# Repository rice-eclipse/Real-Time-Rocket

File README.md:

# Neutro Board
Repository stored on the raspberry pi used for Spaceport America Cup 2023 and launch test in Spring 2023. The scripts activates the sensors on Neutro, collects data, and transmit to the ground station NARWAL.

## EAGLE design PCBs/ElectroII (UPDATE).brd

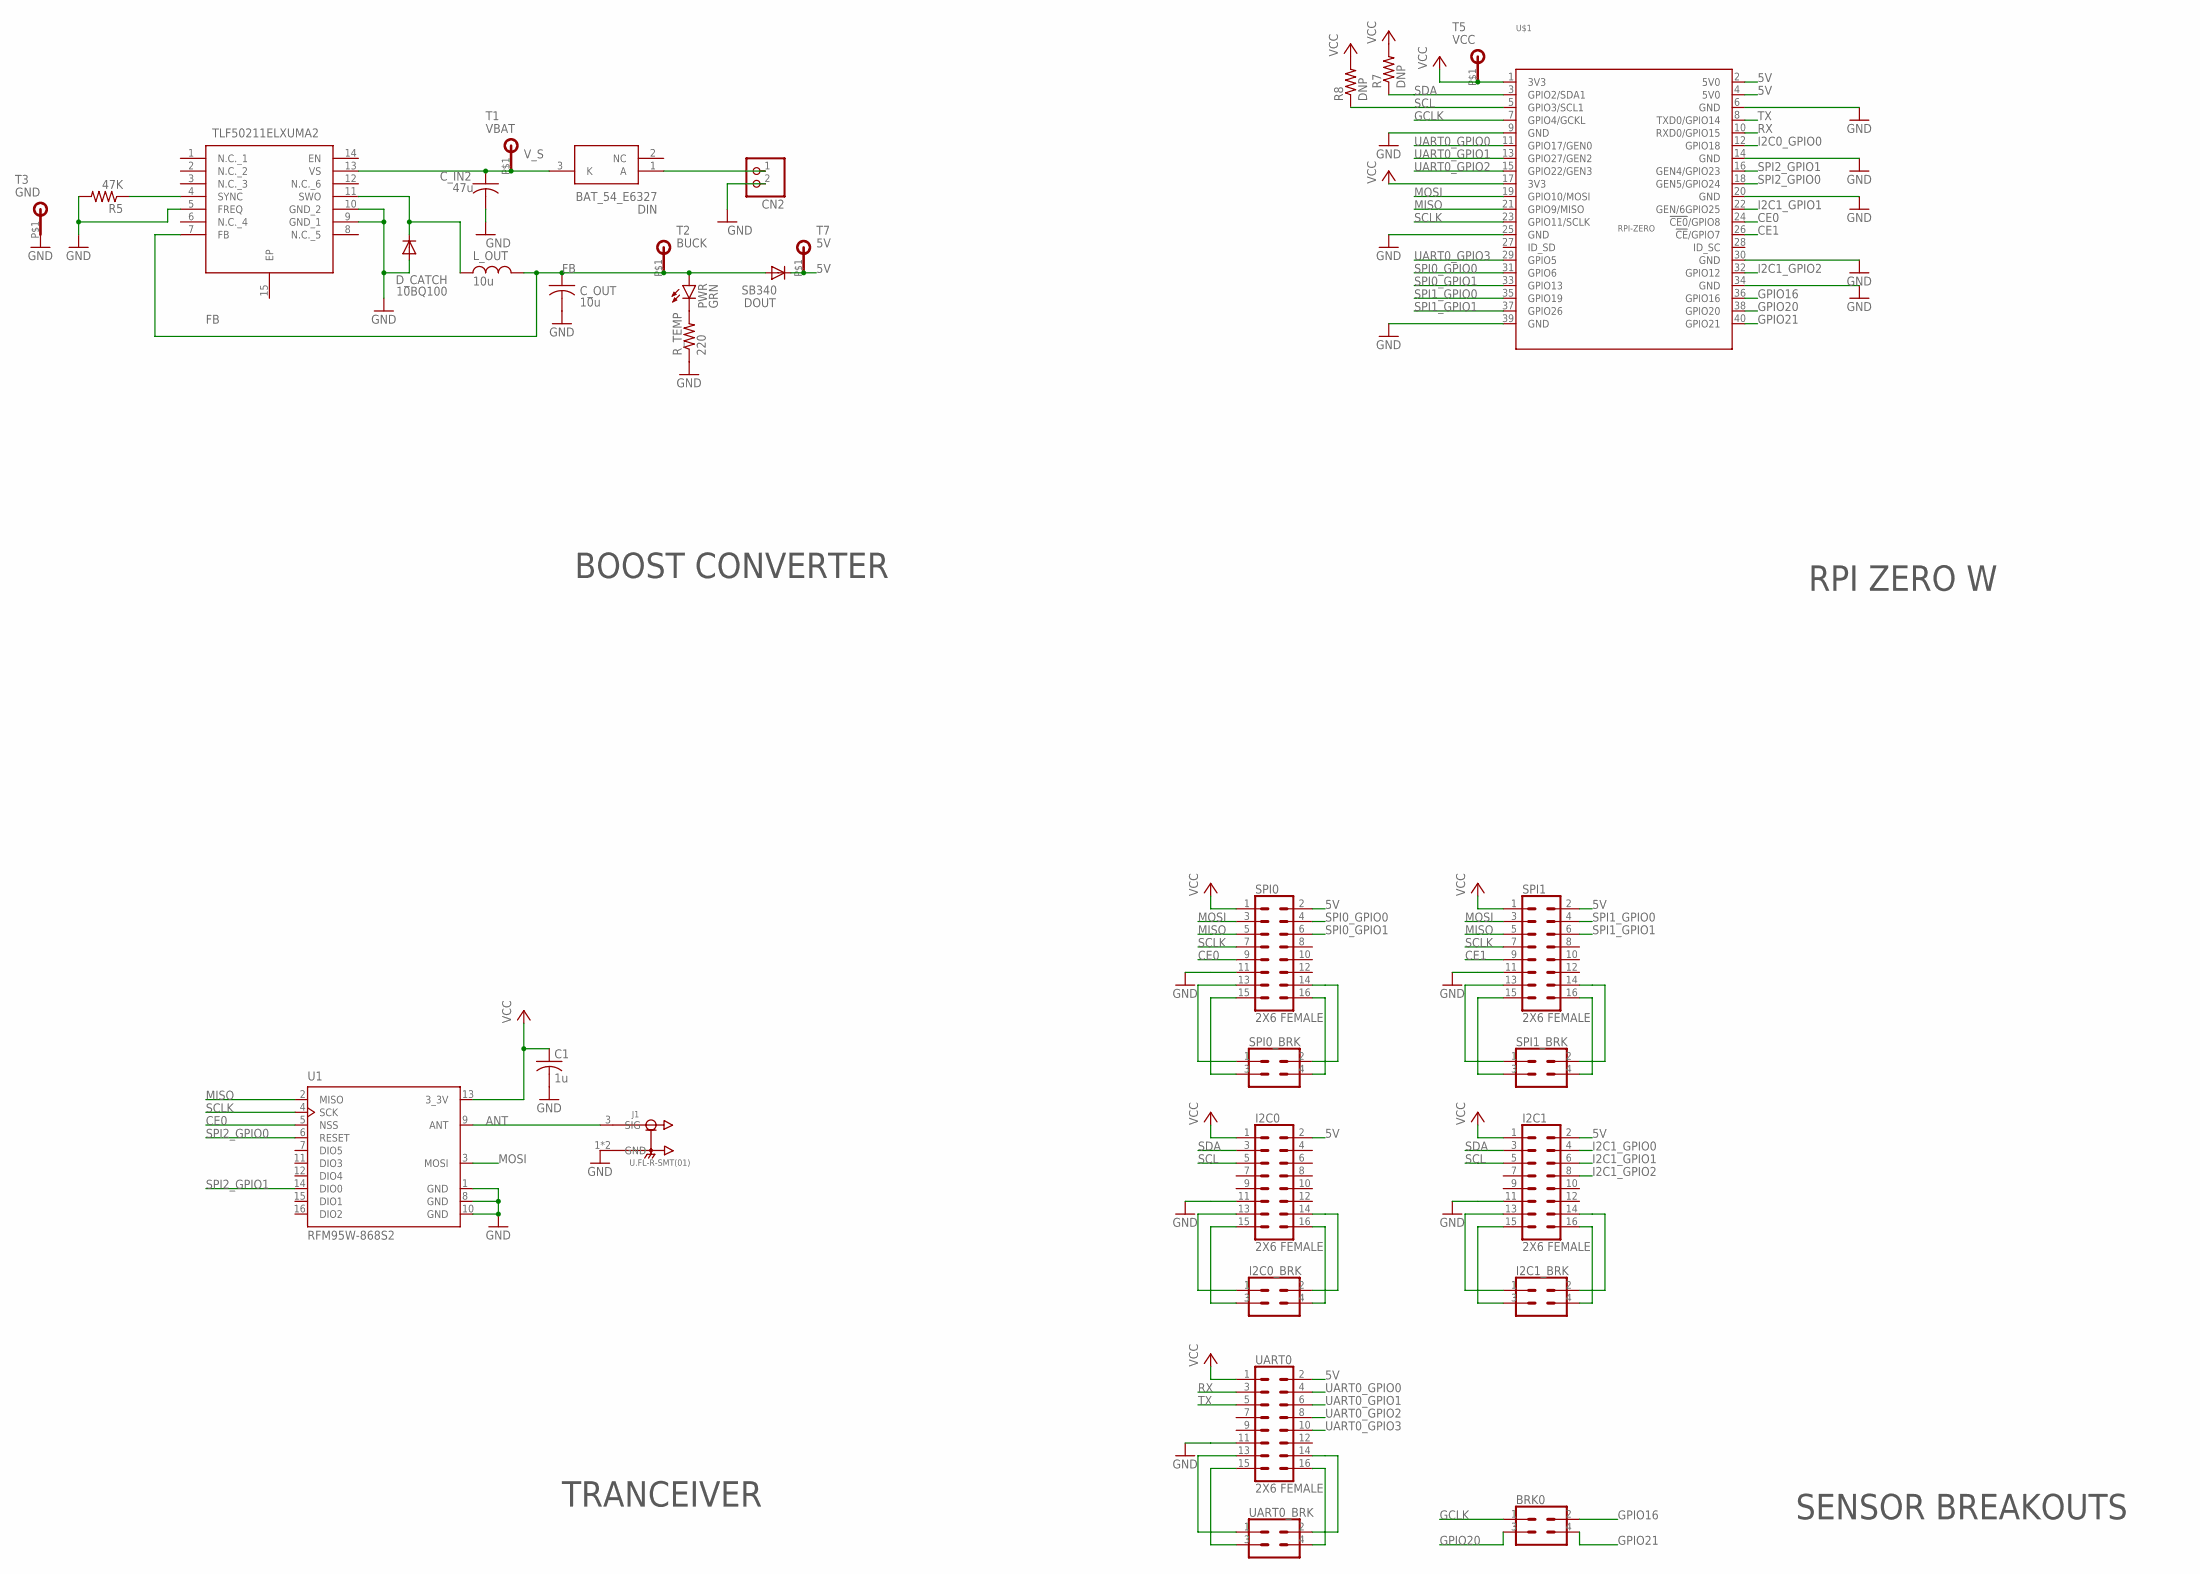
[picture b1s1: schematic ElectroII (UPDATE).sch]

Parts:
BRK0: SENSOR_PIN_BREAKOUT; 2X2
C1: 1u; C1206
CN2: JST_2PIN-SMT-RA; JST-PH-2-SMT-RA
C_IN2: 47u; C1206
C_OUT: 10u; C1206
DIN: BAT_54_E6327; SOT95P240X110-3N
DOUT: SB340; DO41-10
D_CATCH: 10BQ100; DO41-10
I2C0, I2C1: 2X6 FEMALE; 2X7
I2C0_BRK, I2C1_BRK: SENSOR_PIN_BREAKOUT; 2X2
IC1: TLF50211ELXUMA2; SOP65P600X170-15N
J1: U.FL-R-SMT(01); HRS_U.FL-R-SMT(01)
L_OUT: 10u; L-DS75LC
PWR: GRN; LED5MM
R5: 47K; R1206
R7, R8: DNP; R1206
R_TEMP: 220; R1206
SPI0, SPI1: 2X6 FEMALE; 2X7
SPI0_BRK, SPI1_BRK: SENSOR_PIN_BREAKOUT; 2X2
T1: VBAT; TEST_PAD
T2: BUCK; TEST_PAD
T3: GND; TEST_PAD
T5: VCC; TEST_PAD
T7: 5V; TEST_PAD
U1: RFM95W-868S2; XCVR_RFM95W-868S2
U$1: RPI-ZERO; RASP_PI_ZERO_BOARD_FULL
UART0: 2X6 FEMALE; 2X7
UART0_BRK: SENSOR_PIN_BREAKOUT; 2X2

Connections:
5V: DOUT.C, I2C0.2, I2C1.2, SPI0.2, SPI1.2, T7.P$1, U$1.2 (5V0), U$1.4 (5V0), UART0.2
ANT: J1.3 (SIG), U1.9 (ANT)
CE0: SPI0.9, U1.5 (NSS), U$1.24 (!CE0!/GPIO8)
CE1: SPI1.9, U$1.26 (!CE!/GPIO7)
FB: C_OUT.1, DOUT.A, IC1.7 (FB), L_OUT.P$2 (2), PWR.A, T2.P$1
GCLK: BRK0.1, U$1.7 (GPIO4/GCKL)
GND: C1.2, CN2.2 (1), C_IN2.2, C_OUT.2, D_CATCH.A, I2C0.11, I2C1.11, IC1.5 (FREQ), IC1.9 (GND_1), IC1.10 (GND_2), J1.1 (GND), J1.2 (GND), R5.2, R_TEMP.1, SPI0.11, SPI1.11, T3.P$1, U1.1 (GND), U1.8 (GND), U1.10 (GND), U$1.6 (GND), U$1.9 (GND), U$1.14 (GND), U$1.20 (GND), U$1.25 (GND), U$1.30 (GND), U$1.34 (GND), U$1.39 (GND), UART0.11
GPIO16: BRK0.2, U$1.36 (GPIO16)
GPIO20: BRK0.3, U$1.38 (GPIO20)
GPIO21: BRK0.4, U$1.40 (GPIO21)
I2C0_GPIO0: U$1.12 (GPIO18)
I2C1_GPIO0: I2C1.4
I2C1_GPIO1: I2C1.6, U$1.22 (GEN/6GPIO25)
I2C1_GPIO2: I2C1.8, U$1.32 (GPIO12)
MISO: SPI0.5, SPI1.5, U1.2 (MISO), U$1.21 (GPIO9/MISO)
MOSI: SPI0.3, SPI1.3, U1.3 (MOSI), U$1.19 (GPIO10/MOSI)
unnamed: CN2.1 (2), DIN.1 (A)
unnamed: IC1.4 (SYNC), R5.1
unnamed: PWR.K (C), R_TEMP.2
unnamed: SPI0.15, SPI0_BRK.3
unnamed: D_CATCH.C, IC1.11 (SWO), L_OUT.P$1 (1)
unnamed: SPI0.16, SPI0_BRK.4
unnamed: SPI1.13, SPI1_BRK.1
unnamed: SPI0.13, SPI0_BRK.1
unnamed: SPI1.14, SPI1_BRK.2
unnamed: SPI0.14, SPI0_BRK.2
unnamed: SPI1.15, SPI1_BRK.3
unnamed: SPI1.16, SPI1_BRK.4
unnamed: I2C0.13, I2C0_BRK.1
unnamed: I2C0.14, I2C0_BRK.2
unnamed: I2C0.15, I2C0_BRK.3
unnamed: I2C0.16, I2C0_BRK.4
unnamed: I2C1.13, I2C1_BRK.1
unnamed: I2C1.14, I2C1_BRK.2
unnamed: I2C1.15, I2C1_BRK.3
unnamed: I2C1.16, I2C1_BRK.4
unnamed: UART0.13, UART0_BRK.1
unnamed: UART0.14, UART0_BRK.2
unnamed: UART0.15, UART0_BRK.3
unnamed: UART0.16, UART0_BRK.4
RX: U$1.10 (RXD0/GPIO15), UART0.3
SCL: I2C0.5, I2C1.5, R8.1, U$1.5 (GPIO3/SCL1)
SCLK: SPI0.7, SPI1.7, U1.4 (SCK), U$1.23 (GPIO11/SCLK)
SDA: I2C0.3, I2C1.3, R7.1, U$1.3 (GPIO2/SDA1)
SPI0_GPIO0: SPI0.4, U$1.31 (GPIO6)
SPI0_GPIO1: SPI0.6, U$1.33 (GPIO13)
SPI1_GPIO0: SPI1.4, U$1.35 (GPIO19)
SPI1_GPIO1: SPI1.6, U$1.37 (GPIO26)
SPI2_GPIO0: U1.6 (RESET), U$1.18 (GEN5/GPIO24)
SPI2_GPIO1: U1.14 (DIO0), U$1.16 (GEN4/GPIO23)
TX: U$1.8 (TXD0/GPIO14), UART0.5
UART0_GPIO0: U$1.11 (GPIO17/GEN0), UART0.4
UART0_GPIO1: U$1.13 (GPIO27/GEN2), UART0.6
UART0_GPIO2: U$1.15 (GPIO22/GEN3), UART0.8
UART0_GPIO3: U$1.29 (GPIO5), UART0.10
VCC: C1.1, I2C0.1, I2C1.1, R7.2, R8.2, SPI0.1, SPI1.1, T5.P$1, U1.13 (3_3V), U$1.1 (3V3), U$1.17 (3V3), UART0.1
V_S: C_IN2.1, DIN.3 (K), IC1.13 (VS), T1.P$1

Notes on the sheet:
SENSOR BREAKOUTS
RPI ZERO W
TRANCEIVER
BOOST CONVERTER

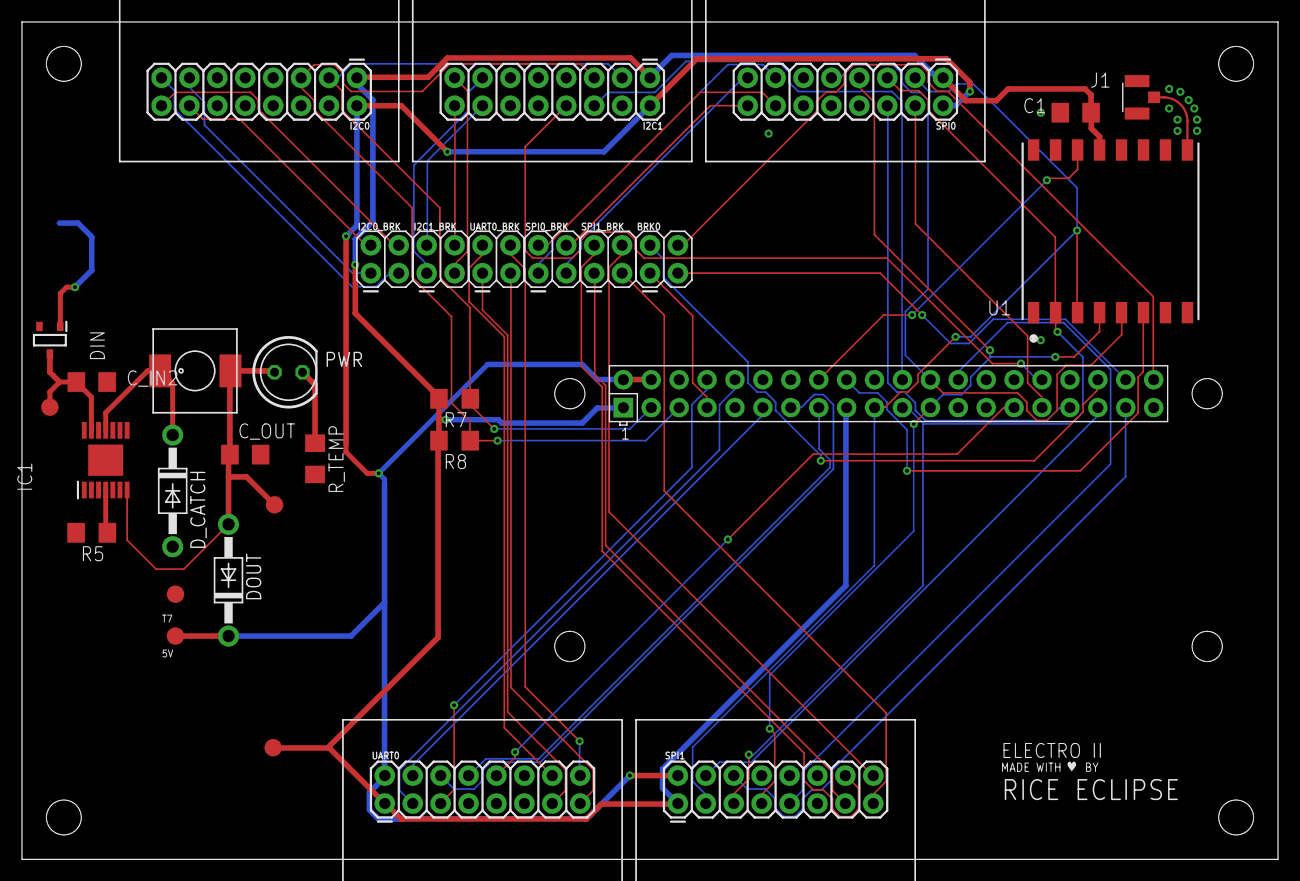
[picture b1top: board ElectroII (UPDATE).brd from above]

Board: 2 copper layers, 114.3 x 76.2 mm, 33 parts (1 on the bottom side), 55 nets.

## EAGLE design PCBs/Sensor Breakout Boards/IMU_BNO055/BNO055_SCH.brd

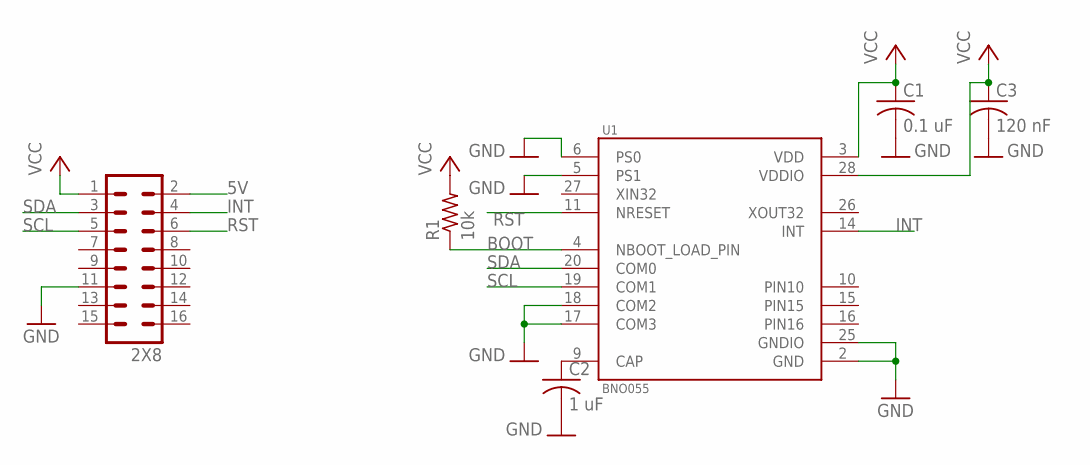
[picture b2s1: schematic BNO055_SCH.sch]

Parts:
2X8: MA08-2
C1: 0.1 uF; C1206
C2: 1 uF; C1206
C3: 120 nF; C1206
R1: 10k; R1206
U1: BNO055; LGA28R50P4X10_380X520X100

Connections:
5V: 2X8.2
BOOT: R1.1, U1.4 (NBOOT_LOAD_PIN)
GND: 2X8.11, C1.2, C2.2, C3.2, U1.2 (GND), U1.5 (PS1), U1.6 (PS0), U1.17 (COM3), U1.18 (COM2), U1.25 (GNDIO)
INT: 2X8.4, U1.14 (INT)
unnamed: C2.1, U1.9 (CAP)
PIN10: U1.10 (PIN10)
PIN15: U1.15 (PIN15)
PIN16: U1.16 (PIN16)
RST: 2X8.6, U1.11 (NRESET)
SCL: 2X8.5, U1.19 (COM1)
SDA: 2X8.3, U1.20 (COM0)
VCC: 2X8.1, C1.1, C3.1, R1.2, U1.3 (VDD), U1.28 (VDDIO)

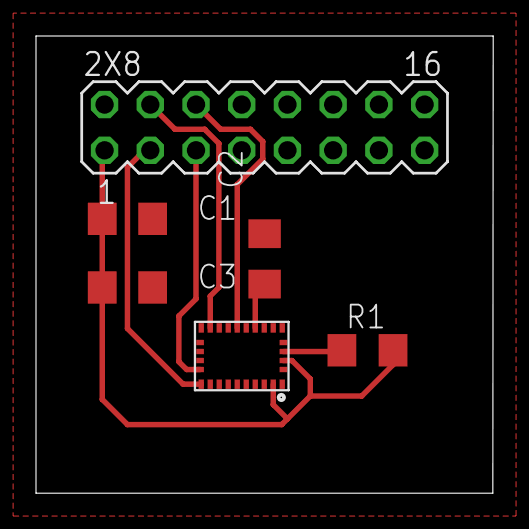
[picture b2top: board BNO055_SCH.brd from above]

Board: 2 copper layers, 25.4 x 25.4 mm, 6 parts (0 on the bottom side), 8 nets.

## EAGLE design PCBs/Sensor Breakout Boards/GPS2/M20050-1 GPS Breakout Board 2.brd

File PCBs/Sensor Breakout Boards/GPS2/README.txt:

Breakout Board for the Antenova GPS (M20050-1).
Plugged into the UART 1/2 Sensor Comm Port
Designed in EAGLE by Clayton Ramsey

Pin Description:
1. V (3v nominal)
2. Unused
3. Tx - output. Transmitter signal for UART.
4. HW_S. Used to enable standby mode.
5. Rx - input. Receiver signal for UART.
6. HW_R. System reset pin, active low
7. Unused
8. TM. Time markout, 1 P/s 
9. Unused
10. FIX - Indicates when a GPS fix is obtained
11. GND
12. Unused
13. Unused
14. Unused
15. Unused
16. Unused

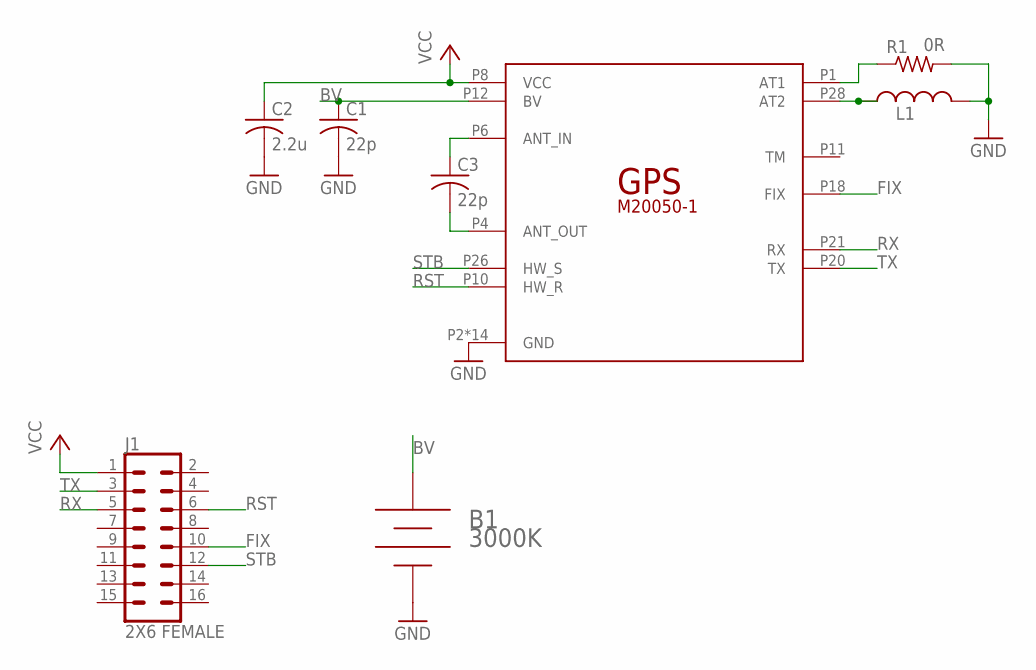
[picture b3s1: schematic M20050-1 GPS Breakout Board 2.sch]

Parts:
A1: GPS_M20050-1; M20050-1_GPS
B1: 3000K
C1, C3: 22p; C1206
C2: 2.2u; C1206
J1: 2X6 FEMALE; 2X7
L1: 1.8n; INDC2012X105N
R1: 0R; R1206

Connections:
BV: A1.P12 (BV), B1.+, C1.1
FIX: A1.P18 (FIX), J1.10
GND: A1.P2 (GND), A1.P3 (GND), A1.P5 (GND), A1.P7 (GND), A1.P9 (GND), A1.P15 (GND), A1.P16 (GND), A1.P17 (GND), A1.P19 (GND), A1.P22 (GND), A1.P23 (GND), A1.P24 (GND), A1.P25 (GND), A1.P27 (GND), B1.-, C1.2, C2.2, L1.2, R1.2
unnamed: A1.P6 (ANT_IN), C3.1
unnamed: A1.P4 (ANT_OUT), C3.2
unnamed: A1.P1 (AT1), R1.1
unnamed: A1.P28 (AT2), L1.1
RST: A1.P10 (HW_R), J1.6
RX: A1.P21 (RX), J1.5
STB: A1.P26 (HW_S), J1.12
TX: A1.P20 (TX), J1.3
VCC: A1.P8 (VCC), C2.1, J1.1

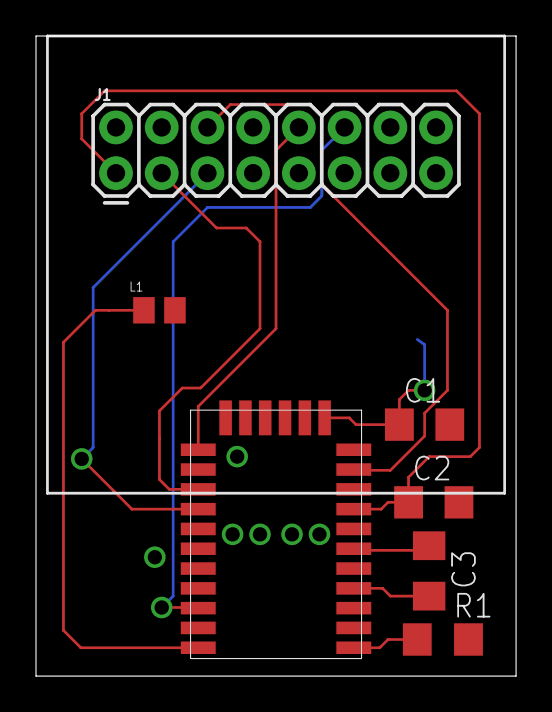
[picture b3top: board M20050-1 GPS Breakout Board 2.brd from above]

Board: 2 copper layers, 26.7 x 35.6 mm, 8 parts (1 on the bottom side), 12 nets.

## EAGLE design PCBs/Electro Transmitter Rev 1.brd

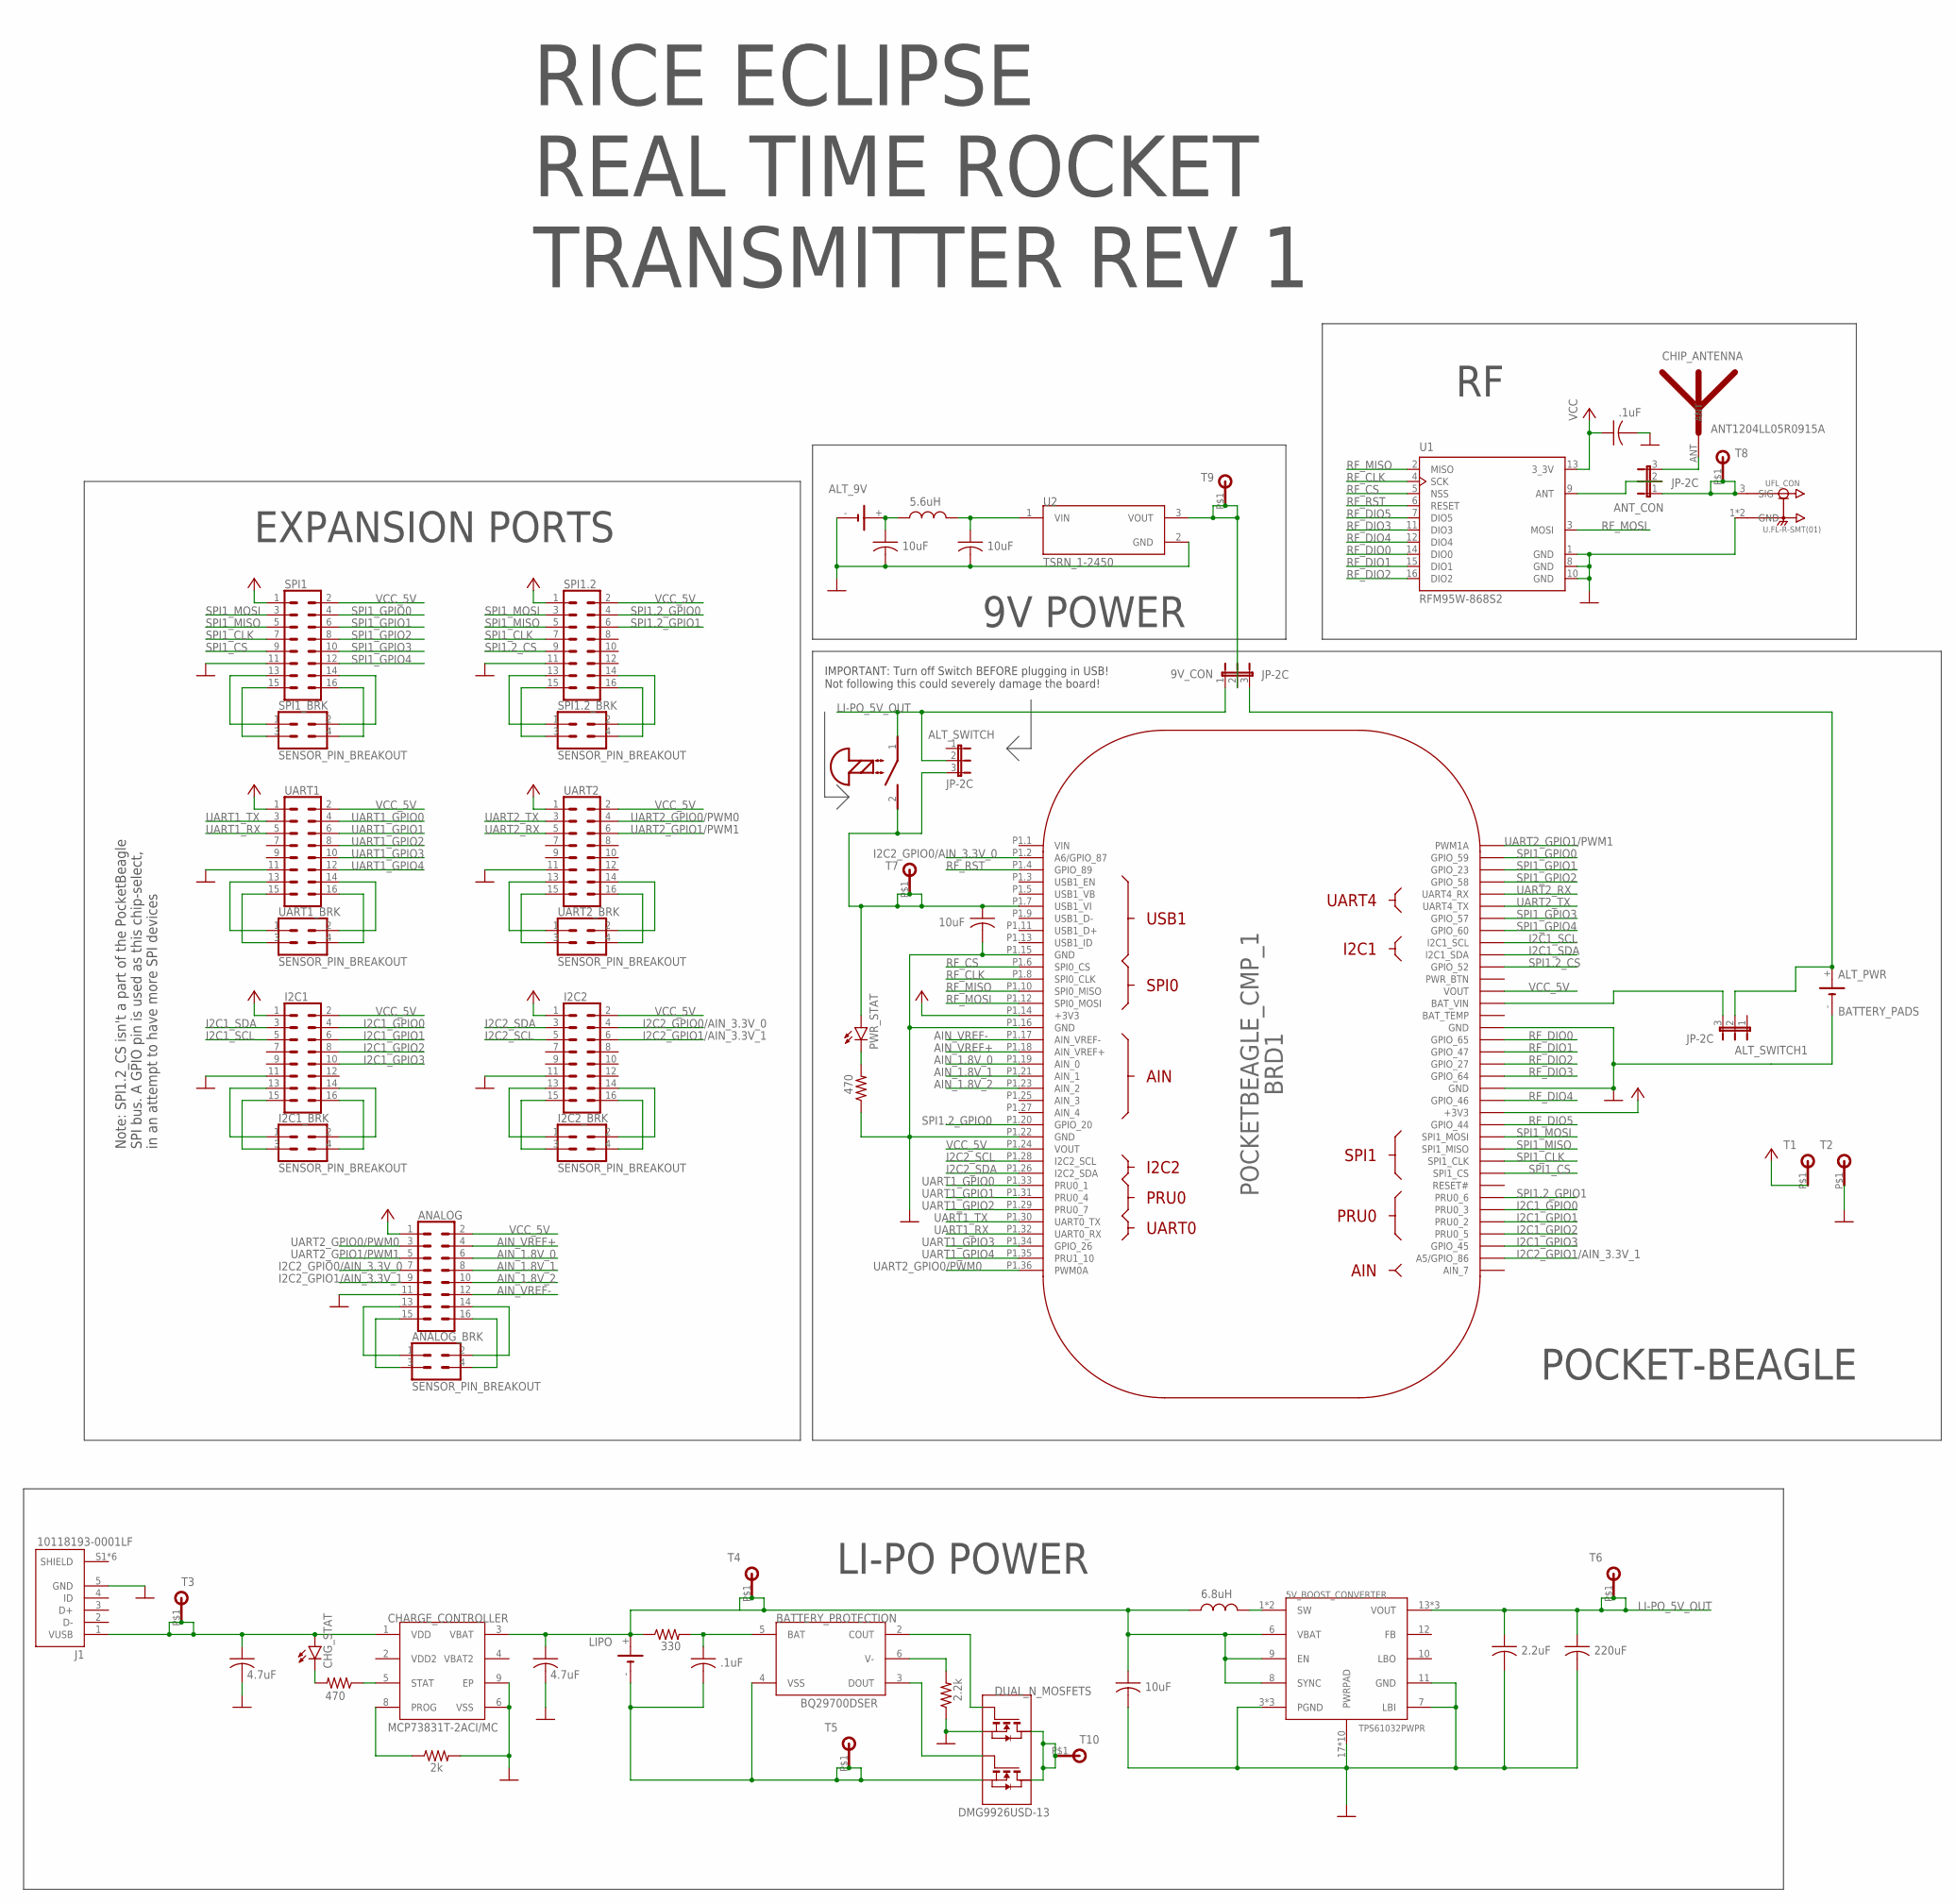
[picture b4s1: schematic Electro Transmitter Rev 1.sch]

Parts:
5V_BOOST_CONVERTER: TPS61032PWPR; SOP65P640X110-17N
9V_C1, 9V_C2: 10uF; C1206
9V_CON: JP-2C; JP2
9V_L1: 5.6uH; L-DS75LC
ALT_9V: BATTERY_PADS; POWER_PADS
ALT_PWR: BATTERY_PADS; POWER_PADS
ALT_SWITCH, ALT_SWITCH1: JP-2C; JP2
ANALOG: 2X6 FEMALE; 2X7
ANALOG_BRK: SENSOR_PIN_BREAKOUT; 2X2
ANT_CON: JP-2C; JP2
BATTERY_PROTECTION: BQ29700DSER; SON50P150X150X80-6N
BAT_C1: .1uF; C1206
BAT_PWR: SCREW_SWITCH
BAT_R1: 330; R1206
BAT_R2: 2.2k; R1206
BRD1: POCKETBEAGLE_CMP_1; POCKETBEAGLE_CMP
CHARGE_CONTROLLER: MCP73831T-2ACI/MC; SON50P200X300X100-9N
CHG_C1, CHG_C2: 4.7uF; C1206
CHG_R1: 470; R1206
CHG_R2: 2k; R1206
CHG_STAT: LED5MM
CHIP_ANTENNA: ANT1204LL05R0915A; SMD_ANTENNA
CONV_C1: 10uF; C1206
CONV_C2: 2.2uF; C1206
CONV_C3: 220uF; C1206
CONV_L1: 6.8uH; L-DS75LC
DUAL_N_MOSFETS: DMG9926USD-13; SOIC127P600X175-8N
I2C1, I2C2: 2X6 FEMALE; 2X7
I2C1_BRK, I2C2_BRK: SENSOR_PIN_BREAKOUT; 2X2
J1: 10118193-0001LF; FCI_10118193-0001LF
LED_R_1: 470; R1206
LIPO: BATTERY_PADS; POWER_PADS
PWR_C1: 10uF; C1206
PWR_STAT: LED5MM
RF_C1: .1uF; C1206
SPI1, SPI1.2: 2X6 FEMALE; 2X7
SPI1.2_BRK, SPI1_BRK: SENSOR_PIN_BREAKOUT; 2X2
T1, T2, T3, T4, T5, T6, T7, T8, T9, T10: TEST_PAD
U1: RFM95W-868S2; XCVR_RFM95W-868S2
U2: TSRN_1-2450; CONV_TSRN_1-2433
UART1, UART2: 2X6 FEMALE; 2X7
UART1_BRK, UART2_BRK: SENSOR_PIN_BREAKOUT; 2X2
UFL_CON: U.FL-R-SMT(01); HRS_U.FL-R-SMT(01)

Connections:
9V_+: 9V_C1.1, 9V_L1.P$1 (1), ALT_9V.+
9V_VIN: 9V_C2.1, 9V_L1.P$2 (2), U2.1 (VIN)
9V_VOUT: 9V_CON.2, T9.P$1, U2.3 (VOUT)
AIN_1.8V_0: ANALOG.6, BRD1.P1.19 (AIN_0)
AIN_1.8V_1: ANALOG.8, BRD1.P1.21 (AIN_1)
AIN_1.8V_2: ANALOG.10, BRD1.P1.23 (AIN_2)
AIN_VREF+: ANALOG.4, BRD1.P1.18 (AIN_VREF+)
AIN_VREF-: ANALOG.12, BRD1.P1.17 (AIN_VREF-)
ALT_PWR_+: 9V_CON.3, ALT_PWR.+, ALT_SWITCH1.2
ANT: ANT_CON.3, CHIP_ANTENNA.ANT
BAT: BATTERY_PROTECTION.5 (BAT), BAT_C1.1, BAT_R1.2
BAT_VIN: ALT_SWITCH1.3, BRD1.P2.14 (BAT_VIN)
COUT: BATTERY_PROTECTION.2 (COUT), DUAL_N_MOSFETS.2 (G1)
DOUT: BATTERY_PROTECTION.3 (DOUT), DUAL_N_MOSFETS.4 (G2)
DRAIN: DUAL_N_MOSFETS.5 (D2), DUAL_N_MOSFETS.6 (D2), DUAL_N_MOSFETS.7 (D1), DUAL_N_MOSFETS.8 (D1), T10.P$1
GND: 5V_BOOST_CONVERTER.3 (PGND), 5V_BOOST_CONVERTER.4 (PGND), 5V_BOOST_CONVERTER.5 (PGND), 5V_BOOST_CONVERTER.7 (LBI), 5V_BOOST_CONVERTER.11 (GND), 5V_BOOST_CONVERTER.17 (PWRPAD), 5V_BOOST_CONVERTER.P$1 (PWRPAD), 5V_BOOST_CONVERTER.P$2 (PWRPAD), 5V_BOOST_CONVERTER.P$3 (PWRPAD), 5V_BOOST_CONVERTER.P$4 (PWRPAD), 5V_BOOST_CONVERTER.P$5 (PWRPAD), 5V_BOOST_CONVERTER.P$6 (PWRPAD), 5V_BOOST_CONVERTER.P$7 (PWRPAD), 5V_BOOST_CONVERTER.P$8 (PWRPAD), 5V_BOOST_CONVERTER.P$9 (PWRPAD), 9V_C1.2, 9V_C2.2, ALT_9V.-, ALT_PWR.-, ANALOG.11, BAT_R2.1, BRD1.P1.15 (GND), BRD1.P1.16 (GND), BRD1.P1.22 (GND), BRD1.P2.15 (GND), BRD1.P2.21 (GND), CHARGE_CONTROLLER.6 (VSS), CHARGE_CONTROLLER.9 (EP), CHG_C1.2, CHG_C2.2, CHG_R2.2, CONV_C1.2, CONV_C2.2, CONV_C3.2, DUAL_N_MOSFETS.1 (S1), I2C1.11, I2C2.11, J1.5 (GND), LED_R_1.1, PWR_C1.2, RF_C1.2, SPI1.11, SPI1.2.11, T2.P$1, U1.1 (GND), U1.8 (GND), U1.10 (GND), U2.2 (GND), UART1.11, UART2.11, UFL_CON.1 (GND), UFL_CON.2 (GND)
I2C1_GPIO0: BRD1.P2.30 (PRU0_3), I2C1.4
I2C1_GPIO1: BRD1.P2.32 (PRU0_2), I2C1.6
I2C1_GPIO2: BRD1.P2.34 (PRU0_5), I2C1.8
I2C1_GPIO3: BRD1.P2.33 (GPIO_45), I2C1.10
I2C1_SCL: BRD1.P2.9 (I2C1_SCL), I2C1.5
I2C1_SDA: BRD1.P2.11 (I2C1_SDA), I2C1.3
I2C2_GPIO0/AIN_3.3V_0: ANALOG.7, BRD1.P1.2 (A6/GPIO_87), I2C2.4
I2C2_GPIO1/AIN_3.3V_1: ANALOG.9, BRD1.P2.35 (A5/GPIO_86), I2C2.6
I2C2_SCL: BRD1.P1.28 (I2C2_SCL), I2C2.5
I2C2_SDA: BRD1.P1.26 (I2C2_SDA), I2C2.3
LED: LED_R_1.2, PWR_STAT.K (C)
LED-: CHG_R1.2, CHG_STAT.K (C)
LI-PO_5V_OUT: 5V_BOOST_CONVERTER.13 (VOUT), 5V_BOOST_CONVERTER.14 (VOUT), 5V_BOOST_CONVERTER.15 (VOUT), 9V_CON.1, ALT_SWITCH.2, BAT_PWR.1 (2), CONV_C2.1, CONV_C3.1, T6.P$1
LI-PO_+: 5V_BOOST_CONVERTER.6 (VBAT), 5V_BOOST_CONVERTER.8 (SYNC), 5V_BOOST_CONVERTER.9 (EN), BAT_R1.1, CHARGE_CONTROLLER.3 (VBAT), CHG_C2.1, CONV_C1.1, CONV_L1.P$1 (1), LIPO.+, T4.P$1
LI-PO_-: BATTERY_PROTECTION.4 (VSS), BAT_C1.2, DUAL_N_MOSFETS.3 (S2), LIPO.-, T5.P$1
unnamed: ANT_CON.1, T8.P$1, UFL_CON.3 (SIG)
unnamed: 5V_BOOST_CONVERTER.1 (SW), 5V_BOOST_CONVERTER.2 (SW), CONV_L1.P$2 (2)
unnamed: SPI1.14, SPI1_BRK.2
unnamed: SPI1.13, SPI1_BRK.1
unnamed: SPI1.15, SPI1_BRK.3
unnamed: SPI1.16, SPI1_BRK.4
unnamed: SPI1.2.13, SPI1.2_BRK.1
unnamed: SPI1.2.14, SPI1.2_BRK.2
unnamed: SPI1.2.16, SPI1.2_BRK.4
unnamed: SPI1.2.15, SPI1.2_BRK.3
unnamed: UART1.13, UART1_BRK.1
unnamed: UART1.15, UART1_BRK.3
unnamed: UART1.14, UART1_BRK.2
unnamed: UART1.16, UART1_BRK.4
unnamed: UART2.15, UART2_BRK.3
unnamed: UART2.16, UART2_BRK.4
unnamed: UART2.14, UART2_BRK.2
unnamed: UART2.13, UART2_BRK.1
unnamed: I2C1.16, I2C1_BRK.4
unnamed: I2C1.15, I2C1_BRK.3
unnamed: I2C1.13, I2C1_BRK.1
unnamed: I2C1.14, I2C1_BRK.2
unnamed: I2C2.15, I2C2_BRK.3
unnamed: I2C2.16, I2C2_BRK.4
unnamed: I2C2.14, I2C2_BRK.2
unnamed: I2C2.13, I2C2_BRK.1
unnamed: ANALOG.15, ANALOG_BRK.3
unnamed: ANALOG.16, ANALOG_BRK.4
unnamed: ANALOG.14, ANALOG_BRK.2
unnamed: ANALOG.13, ANALOG_BRK.1
PROG: CHARGE_CONTROLLER.8 (PROG), CHG_R2.1
RF_ANT: ANT_CON.2, U1.9 (ANT)
RF_CLK: BRD1.P1.8 (SPI0_CLK), U1.4 (SCK)
RF_CS: BRD1.P1.6 (SPI0_CS), U1.5 (NSS)
RF_DIO0: BRD1.P2.17 (GPIO_65), U1.14 (DIO0)
RF_DIO1: BRD1.P2.18 (GPIO_47), U1.15 (DIO1)
RF_DIO2: BRD1.P2.19 (GPIO_27), U1.16 (DIO2)
RF_DIO3: BRD1.P2.20 (GPIO_64), U1.11 (DIO3)
RF_DIO4: BRD1.P2.22 (GPIO_46), U1.12 (DIO4)
RF_DIO5: BRD1.P2.24 (GPIO_44), U1.7 (DIO5)
RF_MISO: BRD1.P1.10 (SPI0_MISO), U1.2 (MISO)
RF_MOSI: BRD1.P1.12 (SPI0_MOSI), U1.3 (MOSI)
RF_RST: BRD1.P1.4 (GPIO_89), U1.6 (RESET)
SPI1.2_CS: BRD1.P2.10 (GPIO_52), SPI1.2.9
SPI1.2_GPIO0: BRD1.P1.20 (GPIO_20), SPI1.2.4
SPI1.2_GPIO1: BRD1.P2.28 (PRU0_6), SPI1.2.6
SPI1_CLK: BRD1.P2.29 (SPI1_CLK), SPI1.7, SPI1.2.7
SPI1_CS: BRD1.P2.31 (SPI1_CS), SPI1.9
SPI1_GPIO0: BRD1.P2.2 (GPIO_59), SPI1.4
SPI1_GPIO1: BRD1.P2.3 (GPIO_23), SPI1.6
SPI1_GPIO2: BRD1.P2.4 (GPIO_58), SPI1.8
SPI1_GPIO3: BRD1.P2.6 (GPIO_57), SPI1.10
SPI1_GPIO4: BRD1.P2.8 (GPIO_60), SPI1.12
SPI1_MISO: BRD1.P2.27 (SPI1_MISO), SPI1.5, SPI1.2.5
SPI1_MOSI: BRD1.P2.25 (SPI1_MOSI), SPI1.3, SPI1.2.3
STAT: CHARGE_CONTROLLER.5 (STAT), CHG_R1.1
SWITCH_5V: ALT_SWITCH.3, BAT_PWR.2 (1), BRD1.P1.7 (USB1_VI), PWR_C1.1, PWR_STAT.A, T7.P$1
UART1_GPIO0: BRD1.P1.33 (PRU0_1), UART1.4
UART1_GPIO1: BRD1.P1.31 (PRU0_4), UART1.6
UART1_GPIO2: BRD1.P1.29 (PRU0_7), UART1.8
UART1_GPIO3: BRD1.P1.34 (GPIO_26), UART1.10
UART1_GPIO4: BRD1.P1.35 (PRU1_10), UART1.12
UART1_RX: BRD1.P1.32 (UART0_RX), UART1.5
UART1_TX: BRD1.P1.30 (UART0_TX), UART1.3
UART2_GPIO0/PWM0: ANALOG.3, BRD1.P1.36 (PWM0A), UART2.4
UART2_GPIO1/PWM1: ANALOG.5, BRD1.P2.1 (PWM1A), UART2.6
UART2_RX: BRD1.P2.5 (UART4_RX), UART2.5
UART2_TX: BRD1.P2.7 (UART4_TX), UART2.3
V-: BATTERY_PROTECTION.6 (V-), BAT_R2.2
VBAT2: CHARGE_CONTROLLER.4 (VBAT2)
VCC: ANALOG.1, BRD1.P1.14 (+3V3), BRD1.P2.23 (+3V3), I2C1.1, I2C2.1, RF_C1.1, SPI1.1, SPI1.2.1, T1.P$1, U1.13 (3_3V), UART1.1, UART2.1
VCC_5V: ANALOG.2, BRD1.P1.24 (VOUT), BRD1.P2.13 (VOUT), I2C1.2, I2C2.2, SPI1.2, SPI1.2.2, UART1.2, UART2.2
VDD2: CHARGE_CONTROLLER.2 (VDD2)
V_USB: CHARGE_CONTROLLER.1 (VDD), CHG_C1.1, CHG_STAT.A, J1.1 (VUSB), T3.P$1

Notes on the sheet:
Note: SPI1.2_CS isn't a part of the PocketBeagle SPI bus. A GPIO pin is used as this chip-select, in an attempt to have more SPI devices
LI-PO POWER
EXPANSION PORTS
9V POWER
POCKET-BEAGLE
RICE ECLIPSE REAL TIME ROCKET TRANSMITTER REV 1
IMPORTANT: Turn off Switch BEFORE plugging in USB! Not following this could severely damage the board!

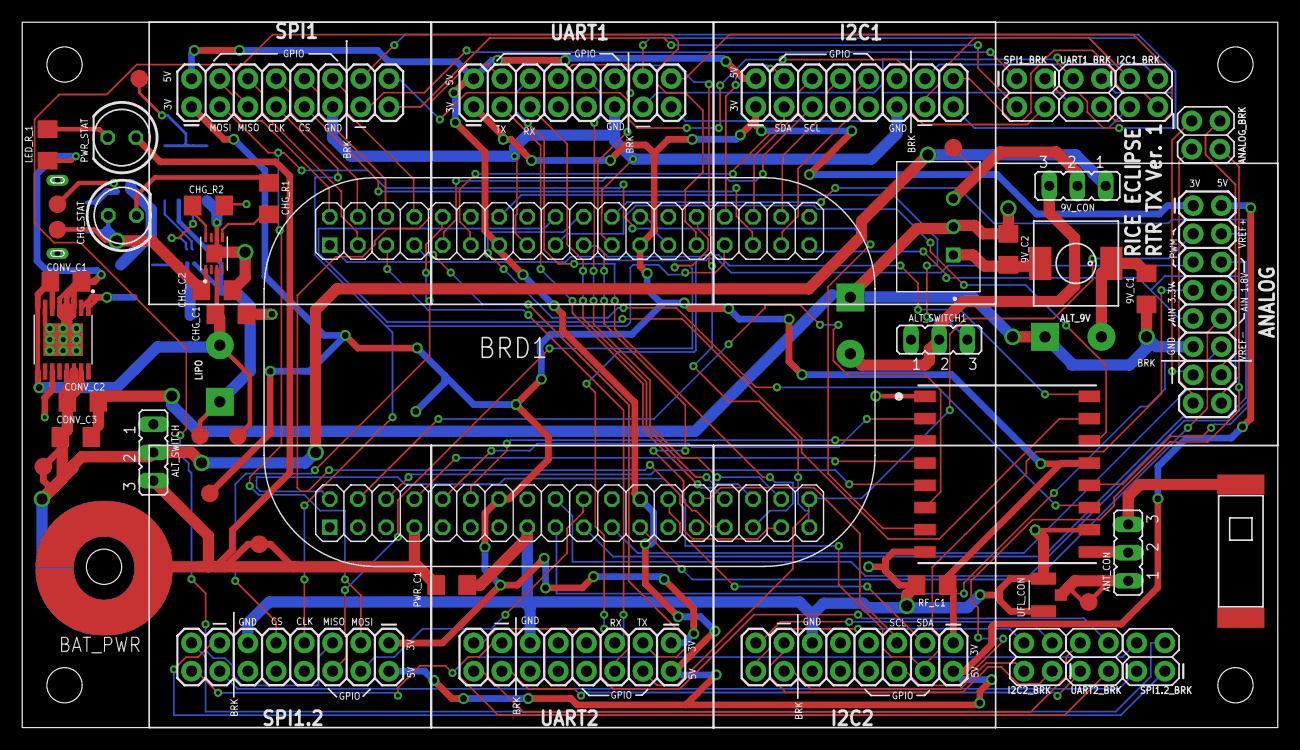
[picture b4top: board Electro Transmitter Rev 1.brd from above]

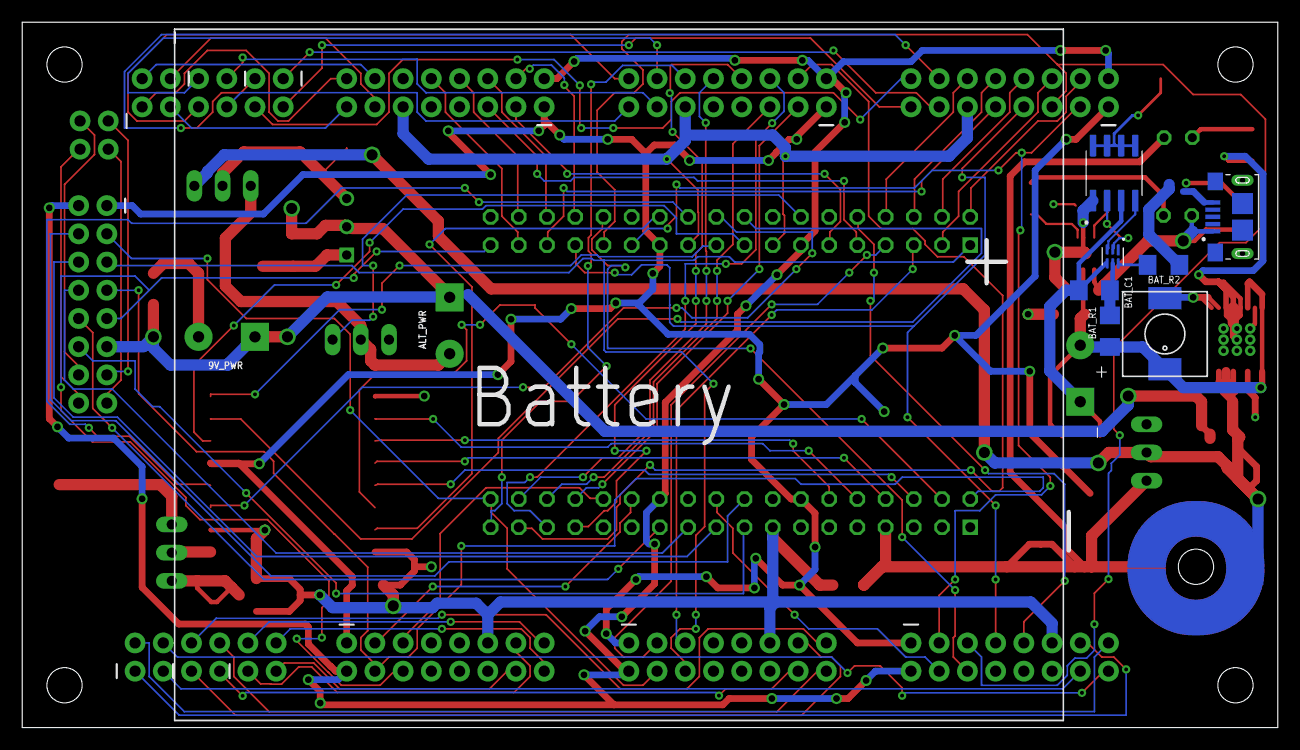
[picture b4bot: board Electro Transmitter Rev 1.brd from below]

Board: 2 copper layers, 113.0 x 63.5 mm, 62 parts (9 on the bottom side), 103 nets.

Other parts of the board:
U$1: 5000MAH_LI-PO_BATTERY

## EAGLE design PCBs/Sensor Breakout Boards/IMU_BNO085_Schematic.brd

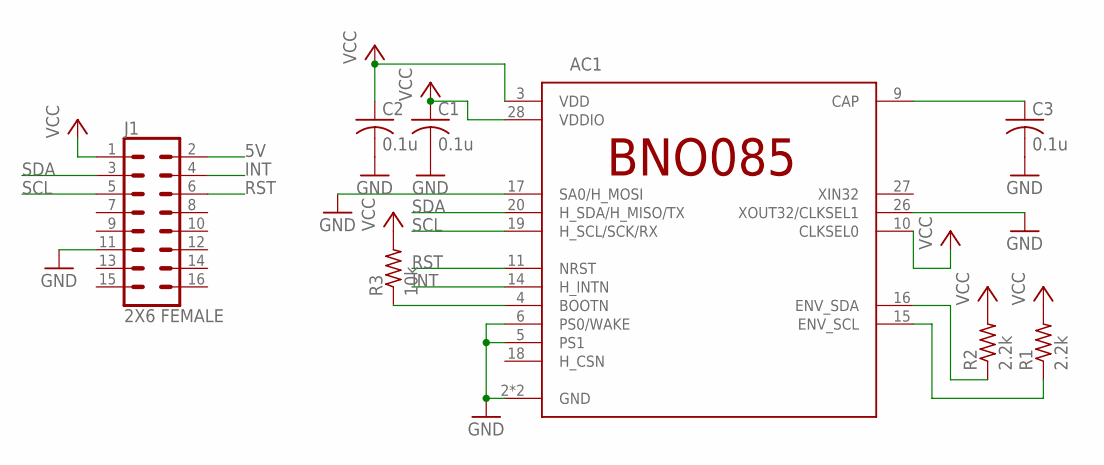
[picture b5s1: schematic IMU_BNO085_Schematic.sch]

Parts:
AC1: BNO085
C1, C2, C3: 0.1u; C1206
J1: 2X6 FEMALE; 2X7
R1, R2: 2.2k; R1206
R3: 10k; R1206

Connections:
5V: J1.2
GND: AC1.2 (GND), AC1.5 (PS1), AC1.6 (PS0/WAKE), AC1.17 (SA0/H_MOSI), AC1.25 (GND), AC1.26 (XOUT32/CLKSEL1), C1.2, C2.2, C3.2, J1.11
INT: AC1.14 (H_INTN), J1.4
unnamed: AC1.16 (ENV_SDA), R2.1
unnamed: AC1.15 (ENV_SCL), R1.1
unnamed: AC1.9 (CAP), C3.1
unnamed: AC1.4 (BOOTN), R3.1
RST: AC1.11 (NRST), J1.6
SCL: AC1.19 (H_SCL/SCK/RX), J1.5
SDA: AC1.20 (H_SDA/H_MISO/TX), J1.3
VCC: AC1.3 (VDD), AC1.10 (CLKSEL0), AC1.28 (VDDIO), C1.1, C2.1, J1.1, R1.2, R2.2, R3.2

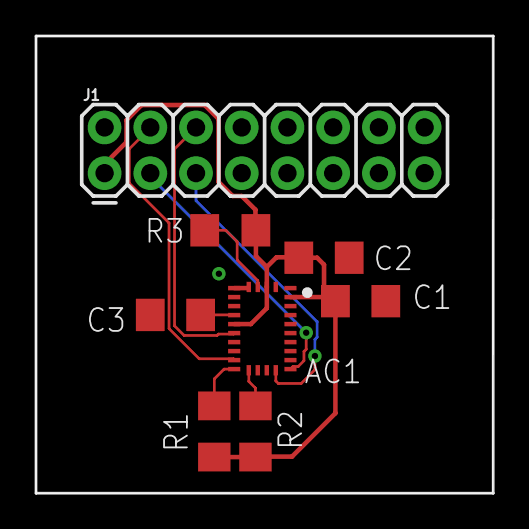
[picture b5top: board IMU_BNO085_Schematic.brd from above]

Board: 2 copper layers, 25.4 x 25.4 mm, 8 parts (0 on the bottom side), 10 nets.

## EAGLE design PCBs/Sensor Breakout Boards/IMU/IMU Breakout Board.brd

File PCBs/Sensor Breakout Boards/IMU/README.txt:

Breakout Board for the InvenSense IMU (ICM-20649).
Plugged into the I2C 1/2 Sensor Comm Port
Designed in EAGLE by Clayton Ramsey

Pin Description:
1. V (3v nominal)
2. Unused
3. SDA - input/output. I2C serial data.
4. FSYNC - input. 
5. SCL - input. I2C clock signal.
6. INT1 - output. Interrupt 1.
7. Unused
8. INT2 - output. Interrupt 2.
9. NCS - input. Chip select (SPI mode)
10. SDO - input. Serial Data Output (SPI mode) or I2C slave address.
11. GND
12. Unused
13. Unused
14. Unused
15. Unused
16. Unused

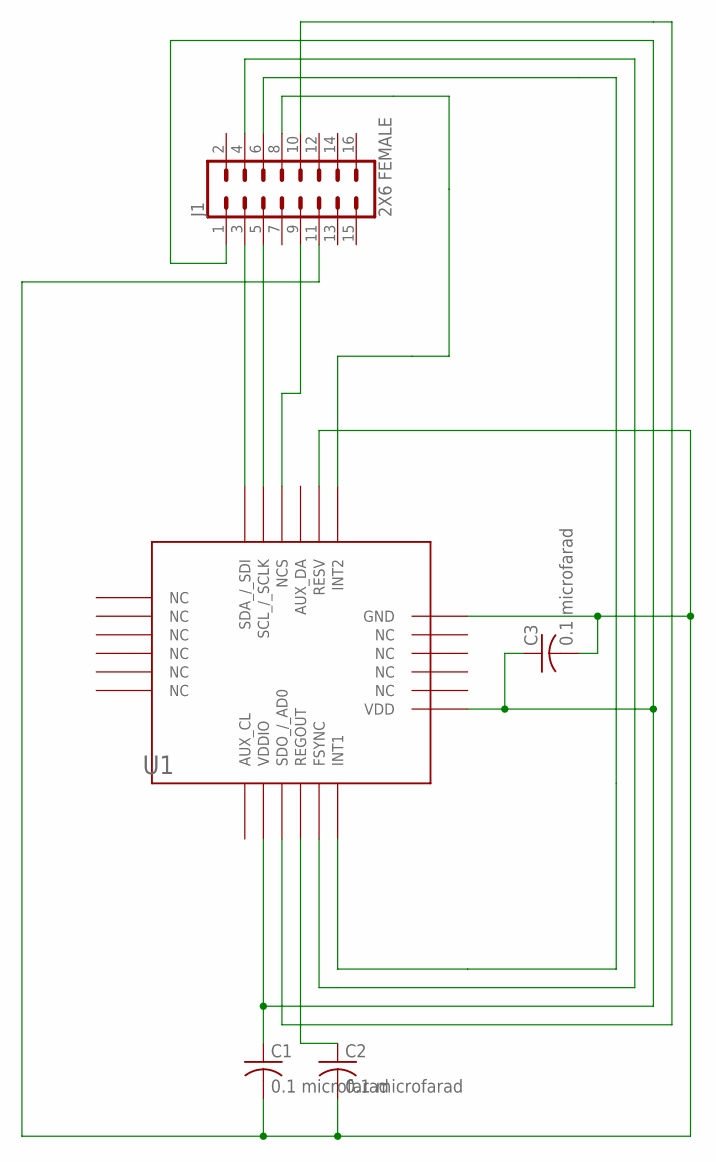
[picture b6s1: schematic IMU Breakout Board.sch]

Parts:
C1, C2, C3: 0.1 microfarad; C1206
J1: 2X6 FEMALE; 2X7
U1: ICM_20649; ICM-20649

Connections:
unnamed: J1.4, U1.P4 (FSYNC)
unnamed: J1.6, U1.P5 (INT1)
unnamed: J1.8, U1.P6 (INT2)
unnamed: J1.9, U1.P9 (NCS)
unnamed: J1.3, U1.P11 (SDA_/_SDI)
unnamed: J1.5, U1.P10 (SCL_/_SCLK)
unnamed: J1.10, U1.P2 (SDO_/_AD0)
unnamed: C1.1, C3.1, J1.1, U1.P1 (VDDIO), U1.P18 (VDD)
unnamed: C2.1, U1.P3 (REGOUT)
unnamed: C1.2, C2.2, C3.2, J1.11, U1.P7 (RESV), U1.P23 (GND)
